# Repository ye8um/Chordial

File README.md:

# Chordial 🎹

## What is Chordial?

Chordial is a small, portable electronic instrument that lets you play musical chords with just a turn and a press of a knob. I wanted to create something that makes playing chords simple and fun, even for someone who doesn't know much about music theory.

Instead of having a full keyboard with dozens of keys, Chordial uses a rotary encoder to choose a chord. Once you've found the chord you want, you can press the knob to hear it play through a built-in speaker.

The whole instrument is designed to fit inside a compact 3D printed enclosure, making it easy to keep on a desk or bring around.

## Why I Made It

I've always found it interesting how different musical notes can come together to create a completely different sound. However, most musical instruments take quite a bit of practice to learn.

That gave me the idea of making an instrument that could play entire chords without needing to learn complicated finger positions.

I also wanted to challenge myself by designing my own PCB, figuring out how electronic components work together, and creating an enclosure that would make everything feel like one complete product.

Chordial combines my interests in music, electronics, programming, and 3D modeling into one project.

## How It Works

Chordial is controlled using two main inputs: a rotary encoder and a mechanical key.

Turning the rotary encoder scrolls through 24 different chords, including all 12 major chords and all 12 minor chords. The selected chord appears on a small OLED display, along with its notes and playback duration.

Pressing the rotary encoder plays the selected chord through the speaker. The sound is generated by the ESP32 and sent to a MAX98357A amplifier, which drives the speaker.

The mechanical key changes how long the chord plays. There are four duration settings: 0.5 seconds, 1 second, 2 seconds, and 4 seconds.

The goal is to make the controls simple enough that anyone can pick up Chordial and start experimenting with different sounds.

## Hardware

Chordial uses a Seeed Studio XIAO ESP32 S3 as its main microcontroller. It handles the rotary encoder, OLED display, and audio generation.

The display is a 128 × 64 SSD1306 OLED, which shows the current chord and its settings.

For sound, I chose a MAX98357A digital audio amplifier connected to an 8 ohm speaker. This allows the instrument to play multiple notes simultaneously and produce a soft, sustained synth sound.

The controls consist of an EC11 rotary encoder with a built-in push button and a Cherry MX compatible mechanical switch.

Chordial is powered by a rechargeable 3.7 V LiPo battery. It also includes a slide switch for controlling battery power, while the XIAO provides USB C connectivity.

All the electronics are designed to fit onto a custom PCB that I made in KiCad.

## Enclosure Design

I designed the enclosure in Fusion 360 with the goal of making Chordial compact, comfortable, and easy to use.

The top has openings for the OLED, rotary encoder, mechanical key, and speaker grille. I also added the Chordial name and an acoustic guitar engraving to give the instrument a little more personality.

The enclosure consists of separate top and bottom pieces that are secured using screws and nuts. The bottom contains compartments for the battery and speaker.

I also plan to use a custom 3D printed rotary knob so the instrument feels more comfortable to control.

## Software

The firmware is written in Arduino C++ for the XIAO ESP32 S3.

It reads the rotary encoder to determine which chord is selected, updates the OLED display, and generates the audio signals needed to play each chord.

Instead of relying on prerecorded audio files, Chordial generates the musical notes directly through code. This means the instrument doesn't need an SD card or stored sound samples.

The firmware currently includes 24 major and minor chords, with four selectable playback durations.

## Building Chordial

I started by creating the schematic and PCB layout in KiCad. This involved figuring out how to connect the microcontroller, amplifier, display, switches, speaker, and battery.

After finishing the PCB design, I created the enclosure in Fusion 360. I had to consider the placement and height of each component to make sure everything would fit together properly.

The firmware was then developed to control the chord selection, display, and sound generation.

The next part of the project is assembling the electronics, testing the firmware on the physical hardware, and making any adjustments needed.

## Bill of Materials

[BOM](BOM.csv)

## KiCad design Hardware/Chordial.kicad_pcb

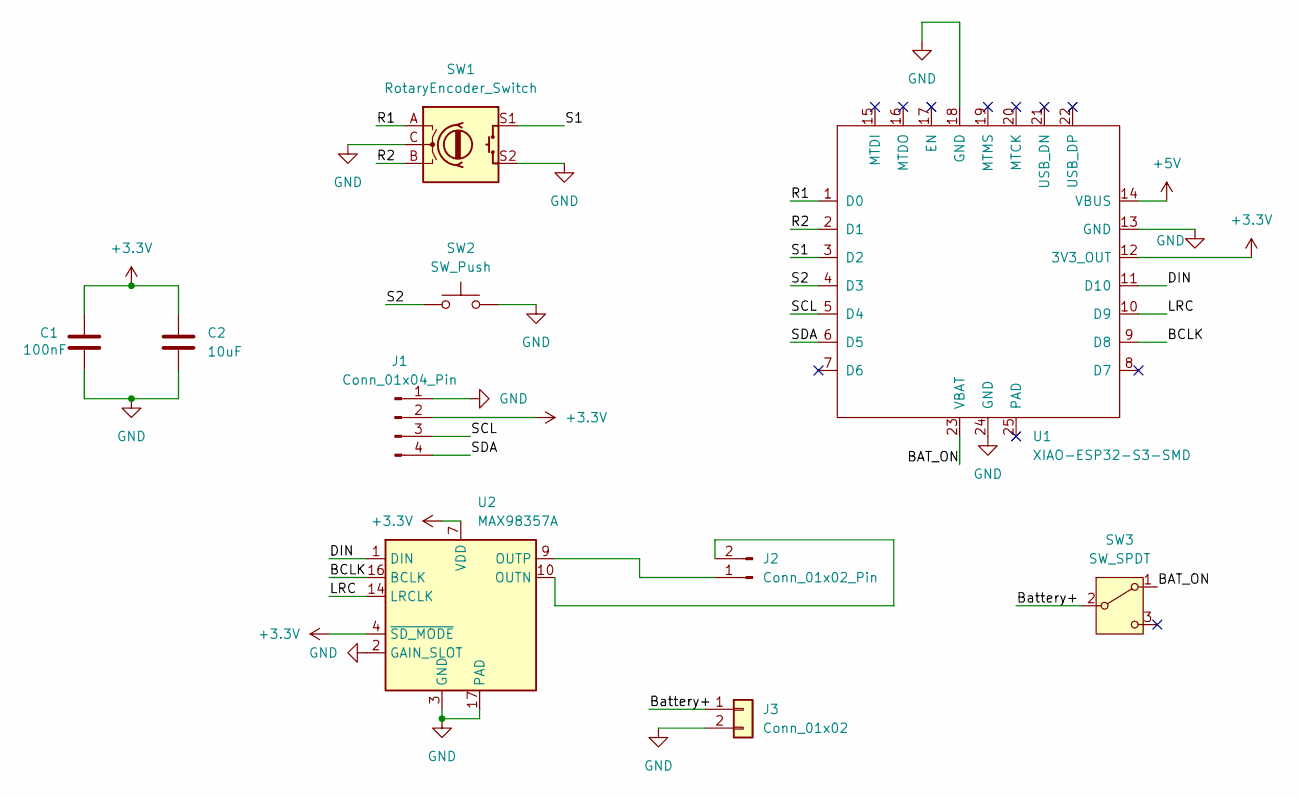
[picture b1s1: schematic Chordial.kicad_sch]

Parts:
C1: 100nF; C_0805_2012Metric
C2: 10uF; C_0805_2012Metric
J1: Conn_01x04_Pin; Display_128x64_096_I2C
J2: Conn_01x02_Pin; Molex_PicoBlade_53261-0271_1x02-1MP_P1.25mm_Horizontal
J3: Conn_01x02; JST_PH_S2B-PH-K_1x02_P2.00mm_Horizontal
SW1: RotaryEncoder_Switch; RotaryEncoder_Alps_EC11E-Switch_Vertical_H20mm_MountingHoles
SW2: SW_Push; SW_Cherry_MX_1.00u_PCB
SW3: SW_SPDT; SW_SPDT_Shouhan_MSK12C02
U1: XIAO-ESP32-S3-SMD
U2: MAX98357A; TQFN-16-1EP_3x3mm_P0.5mm_EP1.23x1.23mm

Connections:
+3.3V: C1.1, C2.1, J1.2, U1.12 (3V3_OUT), U2.4 (~SD_MODE), U2.7 (VDD), U2.8 (VDD)
+5V: U1.14 (VBUS)
/BAT_ON: SW3.1 (A), U1.23 (VBAT)
/BCLK: U1.9 (D8), U2.16 (BCLK)
/Battery+: J3.1, SW3.2 (B)
/DIN: U1.11 (D10), U2.1 (DIN)
/LRC: U1.10 (D9), U2.14 (LRCLK)
/R1: SW1.A, U1.1 (D0)
/R2: SW1.B, U1.2 (D1)
/S1: SW1.S1, U1.3 (D2)
/S2: SW2.1, U1.4 (D3)
/SCL: J1.3, U1.5 (D4)
/SDA: J1.4, U1.6 (D5)
GND: C1.2, C2.2, J1.1, J3.2, SW1.C, SW1.S2, SW2.2, U1.13 (GND), U1.18 (GND), U1.24 (GND), U2.2 (GAIN_SLOT), U2.3 (GND), U2.11 (GND), U2.15 (GND), U2.17 (PAD)
unnamed: J2.1, U2.9 (OUTP)
unnamed: J2.2, U2.10 (OUTN)

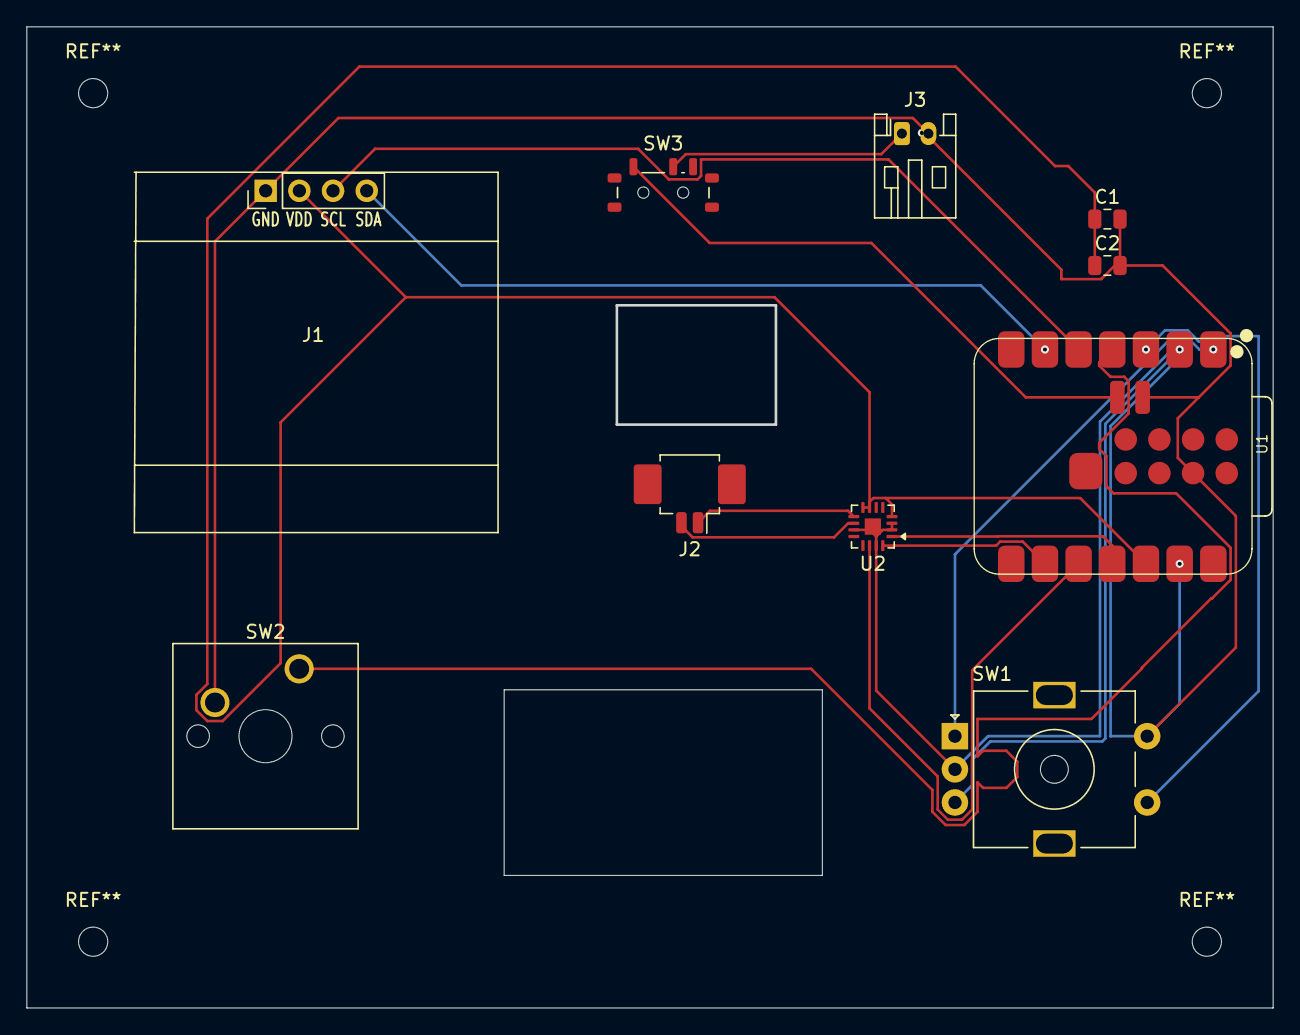
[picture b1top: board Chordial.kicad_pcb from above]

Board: 2 copper layers, 94.0 x 74.0 mm, 10 parts (0 on the bottom side), 15 nets.
